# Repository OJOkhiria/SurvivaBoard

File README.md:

# SurvivaBoard
A custom LoRa board equipped with an ESP32-S3-WROOM-1-N16R8, Ebyte E22-900M22S SX1262 radio, U.FL antenna, U-BLOX MAX M10S 00B GPS module, MMC5983MA magnetometer, BME688 environmental sensor, and a CR2013-MI2120 display driven by an ILI9341 controller. **DISCLAIMER: AI was lightly used to ensure best practices were followed and to speed up research on parts.**

View demos here!: https://drive.google.com/drive/folders/1J8KjE548HSbNNH2rjGCe2-w3qN4_1LWy?dmr=1&ec=wgc-drive-%5Bmodule%5D-goto 

(drive is currently empty because board isn't built yet)

You can view the PCB on your own with https://kicanvas.org/

# Power
Because the board uses a variety of sensors, a GPS, a radio, and other noisy components, I created two separate 3.3V power rails for devices with different noise tolerances. 5V power first comes in from the USB-C receptacle and is stepped down with a fixed-output 3.3V buck converter (ap63203wu-7). To avoid surging, there are TVS diodes on the USB power lines and the D+/D- data lines, and a polyfuse on the power line immediately before the buck converter. The raw output from the buck converter will be used for the ESP32, Ebyte E22-900M22S, and ILI9341. This output also goes through a ferrite bead and an LDO (tlv75533pdrvr) converter to further reduce noise for sensors and other peripherals.

# Subsystems
**ESP32-S3-WROOM-1-N16R8:** Serves as the controller for the entire board. Has a built-in antenna for WiFi and Bluetooth interfacing and communicates with the other various subsystems with UART, SPI, and I²C. It's equipped with an external reset button and plenty of bulk decoupling using 0.1μF and 10μF capacitors.

**U-Blox MAX M10S 00B:** A GPS/GNSS module that will be used to gather data on the board's location and communicate with the ESP32 via UART. Equipped with a TPD1E05U06DPY ESD protection diode; 10μF, 1μF, and 0.1μF decoupling capacitors; and an external coax connector for an active patch antenna (the Quectel YCGO011AA). 

**Ebyte E22-900M22S:** A LoRa module built on the SX1262 transceiver. Originally, I was going to use a bare SX1262, but I chose to go with the Ebyte module to avoid having to build an entire RF front end from scratch. Has an onboard coax connector for an antenna, which will be connected to the FXP290.07.0100A. Communicates with the ESP32 via SPI, and may be used for Meshtastic integration.

**MMC5983MA:** The magnetometer of the board. It will provide heading information to provide the board with a built-in compass. Communicates with the ESP32 using I²C, and has 1μF and 10μF decoupling capacitors.

**BME688:** An environmental sensor that measures temperature, humidity, barometric pressure, and VOC gases. It can generate IAQ (indoor air quality) and also has integrated artificial intelligence, which will be trained to recognize certain odors/gas signatures. Has 0.1μF and 1μF decoupling capacitors and communicates with the ESP32 using I²C.

**ILI9341:** This will be used to display all the information the board gathers, and potentially for users to use Meshtastic. Has an SD card interface for any fonts or other things, and a PWM backlight control. Has 0.1μF and 10μF decoupling capacitors and communicates with the ESP32 using SPI.

# PCB Design
I went with an 80mm by 120mm rectangular 4-layer with 5mm radius filleted edges, with the following designations:
* Layer 1: Signals and USB power processing
* Layer 2: Solid ground plane (with some unfilled areas for antenna clearance)
* Layer 3: Bulk power distribution
* Layer 4: Extra signals

The subsystems are separated and clustered with their respective components to shorten routes and minimize noise interference, and some of these areas are demarcated with stitching vias. The display sits at the head of the board with the Ebyte module, I²C sensors, and a logo immediately underneath. Near the equator and to the left of the board sits the ESP32, with the antenna facing the board's edge and ~9mm of copper-free clearance on both sides of the antenna. On the right is a 25x25mm copper-free clearance zone to (hopefully) mount the Quectel YCGO011AA. In the bottom left is the MAX M10S with a U.FL coax connector, and in the bottom right is the USB-C receptacle and the power systems.

# Bill of Materials

|Reference|Qty|Value|DNP|Exclude from BOM|Exclude from Board|Footprint|Datasheet|
|---|---|---|---|---|---|---|---|
|AE1|1|Antenna| | | | | |
|C6,C9,C12,C15,C19,C23,C25,C27,C29 | 9 | 0.1uF | | | |Capacitor_SMD:C_0603_1608Metric_Pad1.08x0.95mm_HandSolder|
|C7,C13,C22,C26,C28,C30 | 6 | 10uF | | | |Capacitor_SMD:C_0805_2012Metric_Pad1.18x1.45mm_HandSolder| |
|C10,C11 | 2 | 22uF | | | | Capacitor_SMD:C_1206_3216Metric_Pad1.33x1.80mm_HandSolder | |
|C14 | 1 | 2.2uF | | | | Capacitor_SMD:C_0603_1608Metric_Pad1.08x0.95mm_HandSolder | |
|C16,C18,C20 | 3 | 1uF | | | |Capacitor_SMD:C_0603_1608Metric_Pad1.08x0.95mm_HandSolder | |
|C21 | 1 | 47pF | | | | Capacitor_SMD:C_0603_1608Metric_Pad1.08x0.95mm_HandSolder | |
|C24 | 1 | 4.7uF | | | | Capacitor_SMD:C_0603_1608Metric_Pad1.08x0.95mm_HandSolder | |
| D1 | 1 | D_TVS | | | | Diode_SMD:D_SOD-123F| |
|F1 | 1 | Polyfuse | | | | Fuse:Fuse_2920_7451Metric_Pad2.10x5.45mm_HandSolder | |
|FB1 | 1 | FerriteBead | | | | Ferrite_SMD:BEADC1608X95N | |
|IC1 | 1 | E22-900M22S | | | | ebyte:E22-900M22S | |
| J1 | 1 | USB_C_Receptacle_USB2.0_14P | | | | Connector_USB:USB_C_Receptacle_GCT_USB4105-xxA_16P_TopMnt_Horizontal | https://www.usb.org/sites/default/files/documents/usb_type-c.zip|
| J2 | 1 | Conn_Coaxial | | | | Connector_Coaxial:U.FL_Hirose_U.FL-R-SMT-1_Vertical | |
| L2 | 1 | 3.9uH | | | | Inductor_SMD:L_Sunlord_MWSA0402S | |
| L3 | 1 | 27nH | | | | Inductor_SMD:L_0603_1608Metric_Pad1.05x0.95mm_HandSolder | |
| R1,R2 | 2 | 5.1k | | | | Resistor_SMD:R_0603_1608Metric_Pad0.98x0.95mm_HandSolder | |
| R3,R4 | 2 | 4.7k | | | | Resistor_SMD:R_0603_1608Metric_Pad0.98x0.95mm_HandSolder | |
| R5 | 1 | 10k | | | | Resistor_SMD:R_0603_1608Metric_Pad0.98x0.95mm_HandSolder | |
| SW1 | 1 | SW_Push | | | | Tactile_Switch:SW_TS04-66-55-BK-160-SMT | |
| U1 | 1 | ESP32-S3-WROOM-1 | | | | ESP32-S3-WROOM-1-N16R8:ESP32S3WROOM1N8R2 | https://www.espressif.com/sites/default/files/documentation/esp32-s3-wroom-1_wroom-1u_datasheet_en.pdf|
| U2 | 1 | TPD2EUSB30A | | | | USB_ESD:SOTFL35P100X50-3N |http://www.ti.com/lit/ds/symlink/tpd2eusb30a.pdf|
| U3 | 1 | AP63203WU | | | | Buck_Converter:SOIC_05WU-7_DIO-M |https://www.diodes.com/assets/Datasheets/AP63200-AP63201-AP63203-AP63205.pdf|
| U5 | 1 | MAX-M10S | | | | U-BLOX MAX-M10S:XCVR_MAX-M10S-00B | https://content.u-blox.com/sites/default/files/MAX-M10S_DataSheet_UBX-20035208.pdf|
| U6 | 1 | MMC5983MA | | | | MMC5983MA:MMC5983MA_MEM | |
| U7 | 1 | BME688 | | | | BME688:IC_BME688 | |
| U8 | 1 | TLV75533PDRV | | | | LDO:SOT95P280X145-5N |http://www.ti.com/lit/ds/symlink/tlv755p.pdf|
| U9 | 1 | TPD1E05U06DPY | | | | GPS_ESD:DIO_TPD1E05U06DPYR | https://www.ti.com/lit/ds/symlink/tpd1e05u06.pdf|
| U10 | 1 | CR2013-MI2120 | | | | ILI9341:CR2013-MI2120 | http://pan.baidu.com/s/11Y990|

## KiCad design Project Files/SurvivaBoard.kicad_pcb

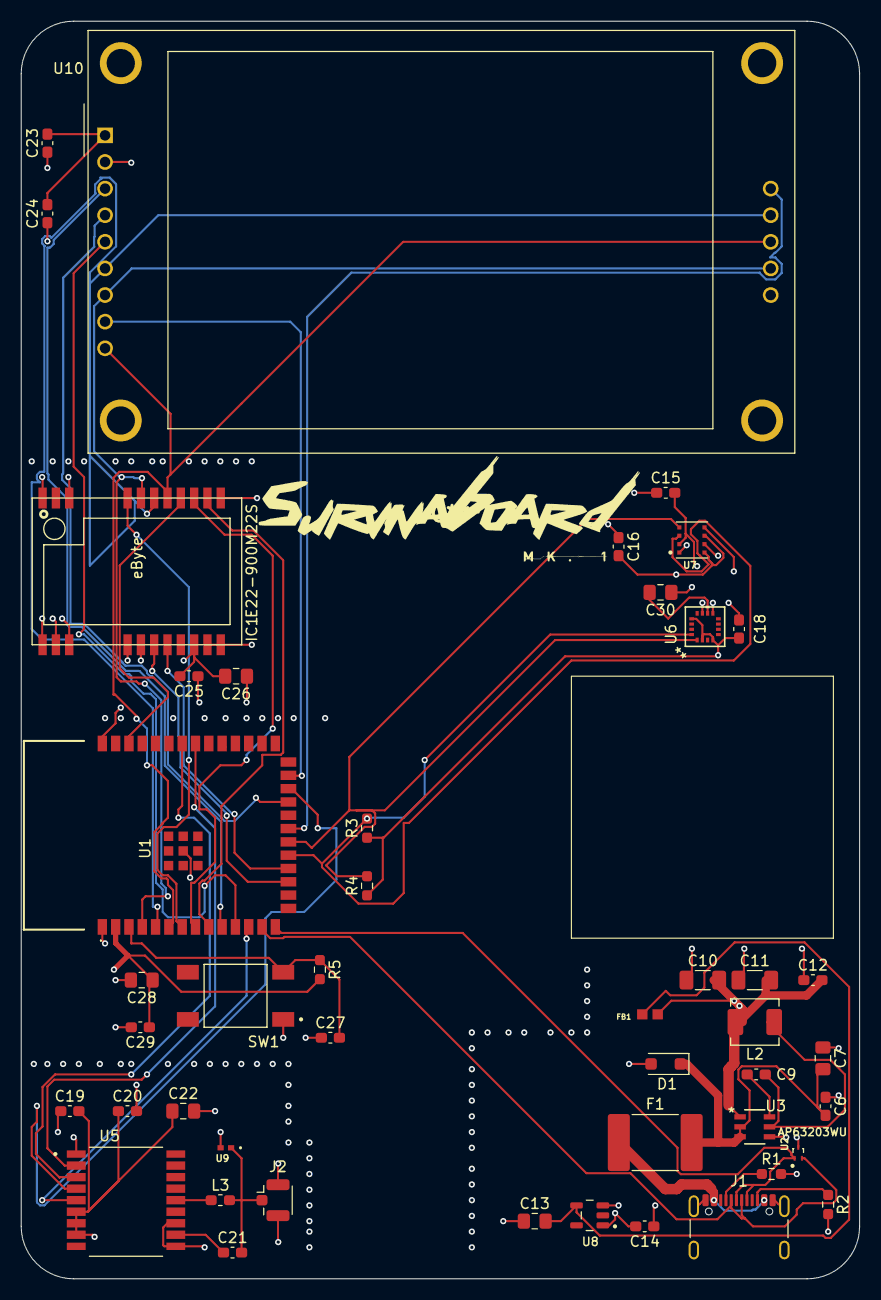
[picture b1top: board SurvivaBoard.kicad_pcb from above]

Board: 4 copper layers, 80.0 x 120.0 mm, 46 parts (0 on the bottom side), 37 nets.

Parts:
C6, C9, C12, C15, C19, C23, C25, C27, C29: 0.1uF; C_0603_1608Metric_Pad1.08x0.95mm_HandSolder
C7, C13, C22, C26, C28, C30: 10uF; C_0805_2012Metric_Pad1.18x1.45mm_HandSolder
C10, C11: 22uF; C_1206_3216Metric_Pad1.33x1.80mm_HandSolder
C14: 2.2uF; C_0603_1608Metric_Pad1.08x0.95mm_HandSolder
C16, C18, C20: 1uF; C_0603_1608Metric_Pad1.08x0.95mm_HandSolder
C21: 47pF; C_0603_1608Metric_Pad1.08x0.95mm_HandSolder
C24: 4.7uF; C_0603_1608Metric_Pad1.08x0.95mm_HandSolder
D1: D_TVS; D_SOD-123F
F1: Polyfuse; Fuse_2920_7451Metric_Pad2.10x5.45mm_HandSolder
FB1: FerriteBead; BEADC1608X95N
IC1: E22-900M22S
J1: USB_C_Receptacle_USB2.0_14P; USB_C_Receptacle_GCT_USB4105-xx-A_16P_TopMnt_Horizontal
J2: Conn_Coaxial; U.FL_Hirose_U.FL-R-SMT-1_Vertical
L2: 3.9uH; L_Sunlord_MWSA0402S
L3: 27nH; L_0603_1608Metric_Pad1.05x0.95mm_HandSolder
R1, R2: 5.1k; R_0603_1608Metric_Pad0.98x0.95mm_HandSolder
R3, R4: 4.7k; R_0603_1608Metric_Pad0.98x0.95mm_HandSolder
R5: 10k; R_0603_1608Metric_Pad0.98x0.95mm_HandSolder
SW1: SW_Push; SW_TS04-66-55-BK-160-SMT
U1: ESP32-S3-WROOM-1; ESP32S3WROOM1N8R2
U2: TPD2EUSB30A; SOTFL35P100X50-3N
U3: AP63203WU; SOIC_05WU-7_DIO-M
U5: MAX-M10S; XCVR_MAX-M10S-00B
U6: MMC5983MA; MMC5983MA_MEM
U7: BME688; IC_BME688
U8: TLV75533PDRV; SOT95P280X145-5N
U9: TPD1E05U06DPY; DIO_TPD1E05U06DPYR
U10: CR2013-MI2120

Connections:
3v3_GPS: C14.2, C15.2, C16.2, C18.2, C19.2, C20.1, C22.1, R3.1, R4.1, U5.6 (V_BCKP), U5.7 (VCC_IO), U5.8 (VCC), U6.2 (VDD), U6.4 (SPI_CS), U6.13 (VDDIO), U7.2 (CSB), U7.6 (VDDIO), U7.8 (VDD), U8.1 (OUT)
3v3_MAIN: C10.2, C11.2, C12.2, C23.2, C24.2, C25.2, C26.2, C28.1, C29.1, FB1.1, IC1.9 (VCC), L2.2, R5.2, U1.2 (3V3), U3.1 (FB), U10.1 (VCC)
BUSY: IC1.14 (BUSY), U1.8 (IO15)
D+: J1.A6 (D+), J1.B6 (D+), U1.14 (USB_D+), U2.1 (D+)
D-: J1.A7 (D-), J1.B7 (D-), U1.13 (USB_D-), U2.2 (D-)
DIO1: IC1.13 (DIO1), U1.9 (IO16)
GND: C6.1, C7.1, C10.1, C11.1, C12.1, C13.1, C14.1, C15.1, C16.1, C18.1, C19.1, C20.2, C22.2, C23.1, C24.1, C25.1, C26.1, C27.1, C28.2, C29.2, C30.1, D1.2 (A2), IC1.1 (GND), IC1.2 (GND), IC1.3 (GND), IC1.4 (GND), IC1.5 (GND), IC1.10 (GND), IC1.11 (GND), IC1.12 (GND), IC1.20 (GND), IC1.22 (GND), J1.A1 (GND), J1.A12 (GND), J1.B1 (GND), J1.B12 (GND), J1.SH (SHIELD), J2.2 (Ext), R1.2, R2.2, SW1.1, U1.1 (GND), U1.40 (GND), U1.41 (GND), U2.3 (GND), U3.4 (GND), U5.1 (GND), U5.10 (GND), U5.12 (GND), U6.9 (GND), U6.11 (GND), U7.1 (GND), U7.5 (SDO), U7.7 (GND), U8.3 (GND), U9.2 (GND), U10.2 (GND)
GPS_EXTINT: U1.12 (IO8), U5.5 (EXTINT)
GPS_TIMEPULSE: U1.24 (IO47), U5.4 (TIMEPULSE)
MISO: IC1.16 (MISO), U1.6 (IO6), U10.9 (MISO), U10.12 (SD_MISO)
MOSI: IC1.17 (MOSI), U1.5 (IO5), U10.6 (MOSI), U10.11 (SD_MOSI)
NSS: IC1.19 (NSS), U1.7 (IO7)
unnamed: C6.2, C7.2, D1.1 (A1), F1.2, U3.2 (EN), U3.3 (IN)
unnamed: F1.1, J1.A4 (VBUS), J1.A9 (VBUS), J1.B4 (VBUS), J1.B9 (VBUS)
unnamed: J1.A5 (CC1), R1.1
unnamed: J1.B5 (CC2), R2.1
unnamed: C21.2, J2.1 (In), L3.2, U9.1 (I/O)
unnamed: C27.2, R5.1, SW1.2, U1.3 (EN)
unnamed: C9.1, U3.6 (BST)
unnamed: C9.2, L2.1, U3.5 (SW)
unnamed: C21.1, U5.11 (RF_IN)
unnamed: L3.1, U5.14 (VCC_RF)
unnamed: C30.2, U6.10 (CAP)
unnamed: C13.2, FB1.2, U8.4 (EN)
RESET: IC1.15 (NRST), U1.38 (IO2)
RX: U1.33 (IO40), U5.2 (TXD)
RXEN: IC1.7 (TXEN), U1.18 (IO10)
SCK: IC1.18 (SCK), U1.4 (IO4), U10.7 (SCK), U10.13 (SD_SCK)
SCL: R4.2, U1.20 (IO12), U6.1 (SCL/SPI_SCK), U7.4 (SCK)
SDA: R3.2, U1.19 (IO11), U6.16 (SDA/SPI_SDI), U7.3 (SDI)
SD_CS: U1.21 (IO13), U10.10 (SD_CS)
TFT_CS: U1.10 (IO17), U10.3 (~CS)
TFT_DC: U1.11 (IO18), U10.5 (D/~C)
TFT_PWM: U1.25 (IO48), U10.8 (LED)
TFT_RST: U1.23 (IO21), U10.4 (RESET)
TX: U1.34 (IO41), U5.3 (RXD)
TXEN: IC1.6 (RXEN), U1.17 (IO9)

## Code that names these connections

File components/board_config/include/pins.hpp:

#pragma once

#include "driver/gpio.h"

namespace board::pins {

inline constexpr gpio_num_t spi_sck  = GPIO_NUM_4;
inline constexpr gpio_num_t spi_mosi = GPIO_NUM_5;
inline constexpr gpio_num_t spi_miso = GPIO_NUM_6;

inline constexpr gpio_num_t lora_reset = GPIO_NUM_3;
inline constexpr gpio_num_t lora_cs    = GPIO_NUM_7;
inline constexpr gpio_num_t gps_extint = GPIO_NUM_8;
inline constexpr gpio_num_t lora_txen  = GPIO_NUM_9;
inline constexpr gpio_num_t lora_rxen  = GPIO_NUM_10;

inline constexpr gpio_num_t i2c_sda = GPIO_NUM_11;
inline constexpr gpio_num_t i2c_scl = GPIO_NUM_12;
inline constexpr gpio_num_t sd_cs = GPIO_NUM_13;

inline constexpr gpio_num_t lora_busy = GPIO_NUM_15;
inline constexpr gpio_num_t lora_dio1 = GPIO_NUM_16;

inline constexpr gpio_num_t tft_cs  = GPIO_NUM_17;
inline constexpr gpio_num_t tft_dc  = GPIO_NUM_18;
inline constexpr gpio_num_t tft_rst = GPIO_NUM_21;
inline constexpr gpio_num_t mag_int = GPIO_NUM_38;

inline constexpr gpio_num_t gps_timepulse = GPIO_NUM_47;
inline constexpr gpio_num_t tft_pwm       = GPIO_NUM_48;

inline constexpr gpio_num_t gps_rx = GPIO_NUM_44; // ESP32 RX <- GPS TX
inline constexpr gpio_num_t gps_tx = GPIO_NUM_43; // ESP32 TX -> GPS RX

} // namespace board::pins
